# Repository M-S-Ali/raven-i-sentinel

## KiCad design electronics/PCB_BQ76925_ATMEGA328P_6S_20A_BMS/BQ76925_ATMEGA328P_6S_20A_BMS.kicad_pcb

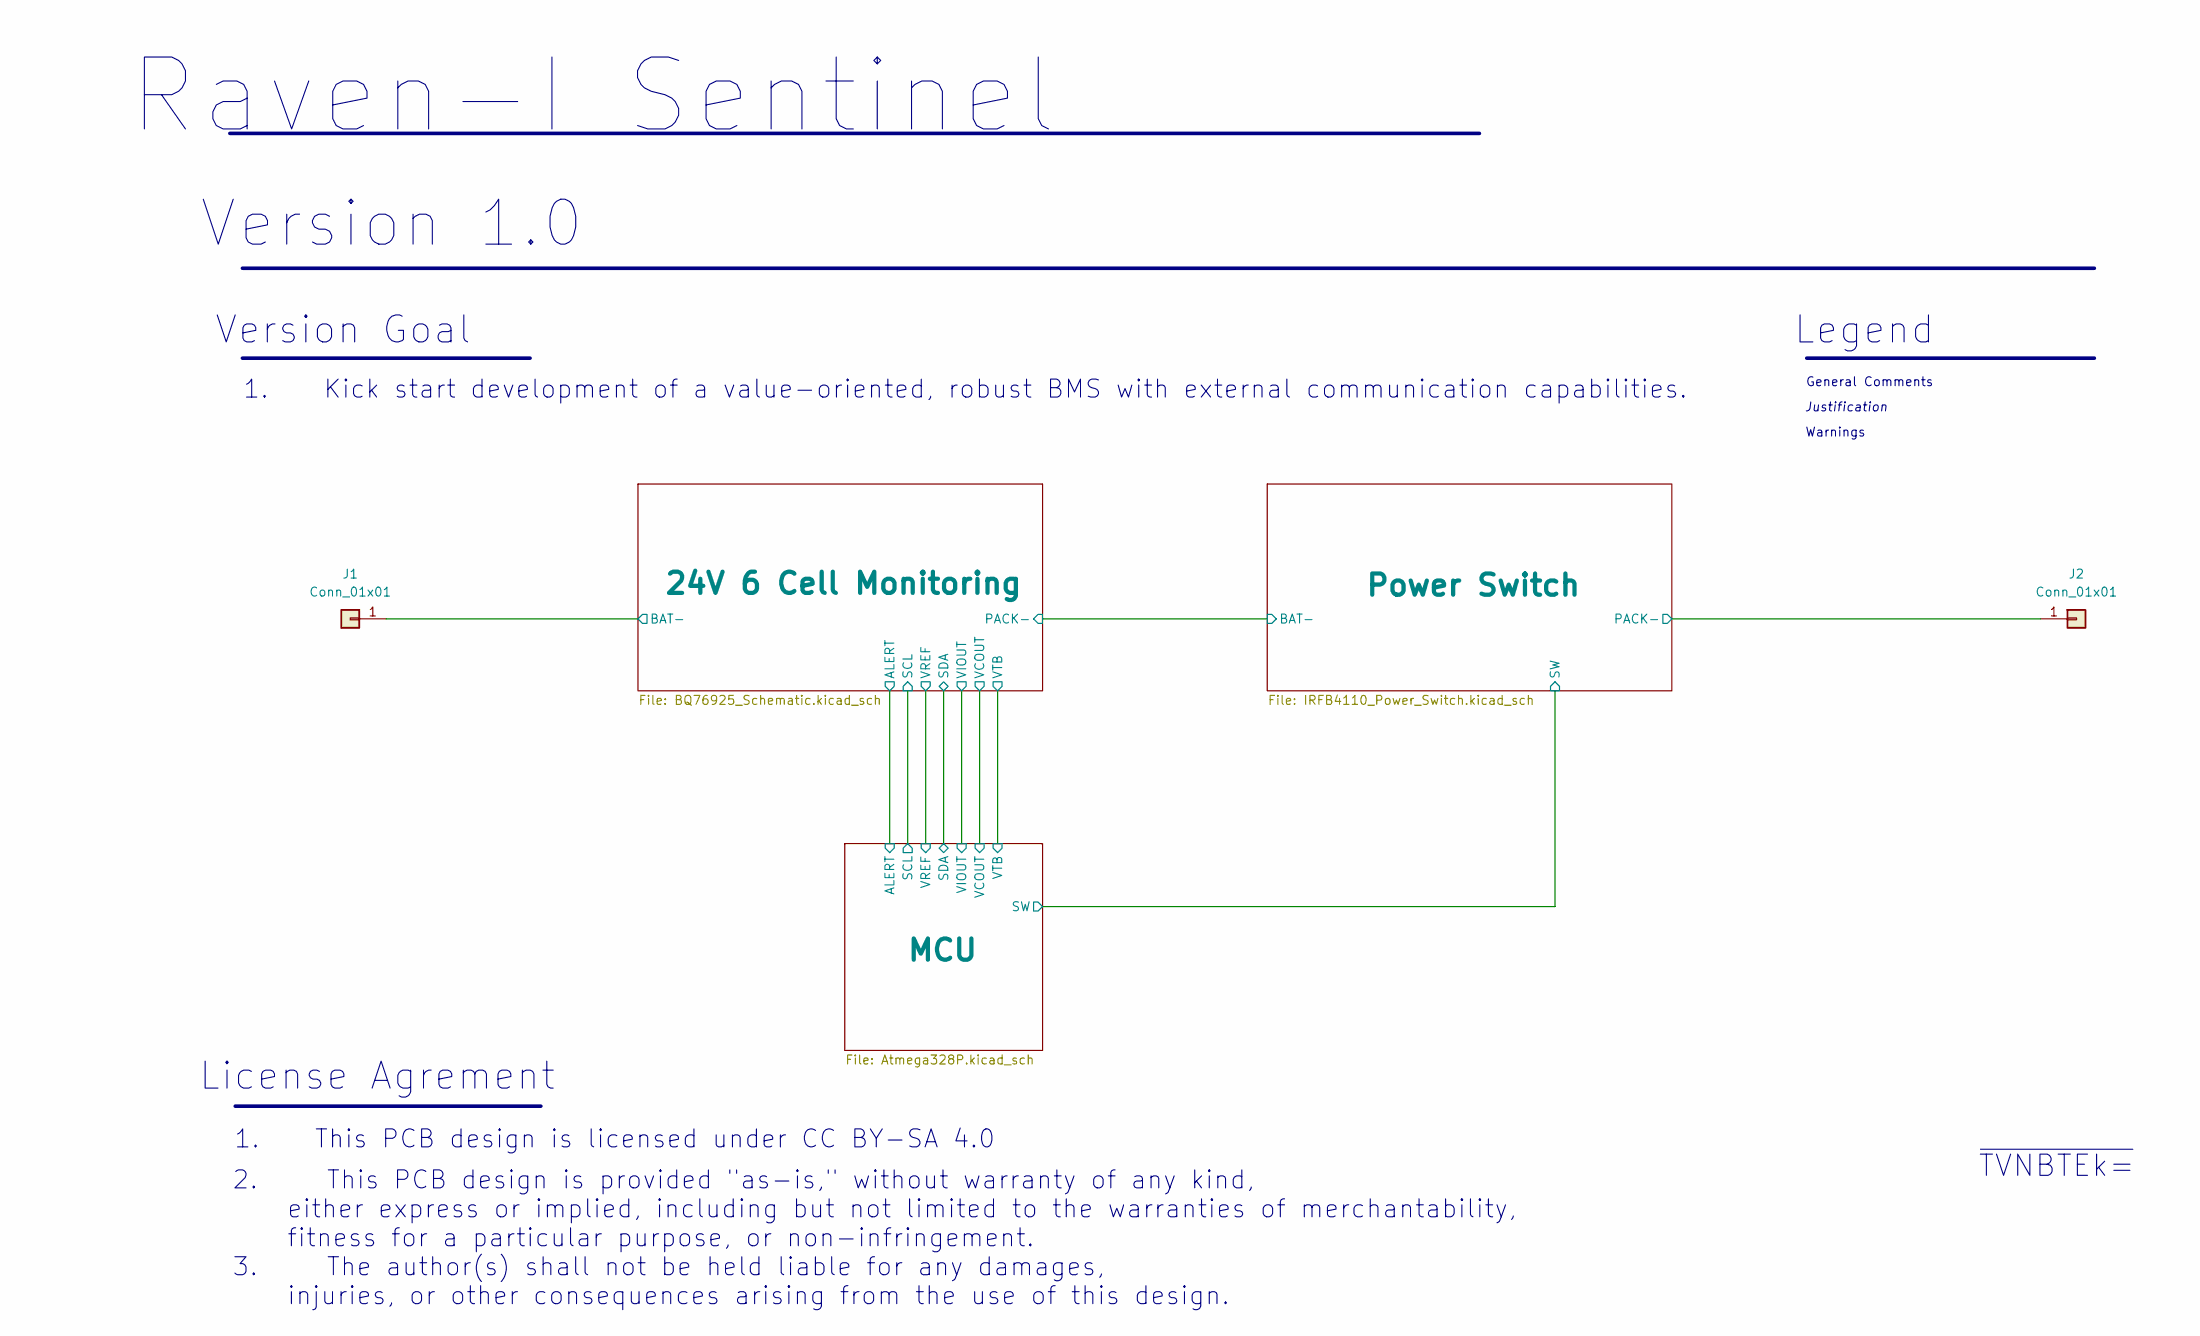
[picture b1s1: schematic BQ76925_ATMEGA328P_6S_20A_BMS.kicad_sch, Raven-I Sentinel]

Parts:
J1, J2: Conn_01x01; SolderWirePad_1x01_SMD_5x10mm

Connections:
/24V 6 Cell Monitoring/BAT-: J1.1; also elsewhere on the board
/Power Switch/PACK-: J2.1; also elsewhere on the board

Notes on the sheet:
1. This PCB design is licensed under CC BY-SA 4.0
Justification
1. Kick start development of a value-oriented, robust BMS with external communication capabilities.
~{TVNBTEk=}
License Agrement
Warnings
2. This PCB design is provided "as-is," without warranty of any kind, either express or implied, including but not limited to the warranties of merchantability, fitness for a particular purpose, or non-infringement. 3. The author(s) shall not be held liable for any damages, injuries, or other conse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
General Comments
Version ${REVISION}
Raven-I Sentinel
Version Goal
Legend

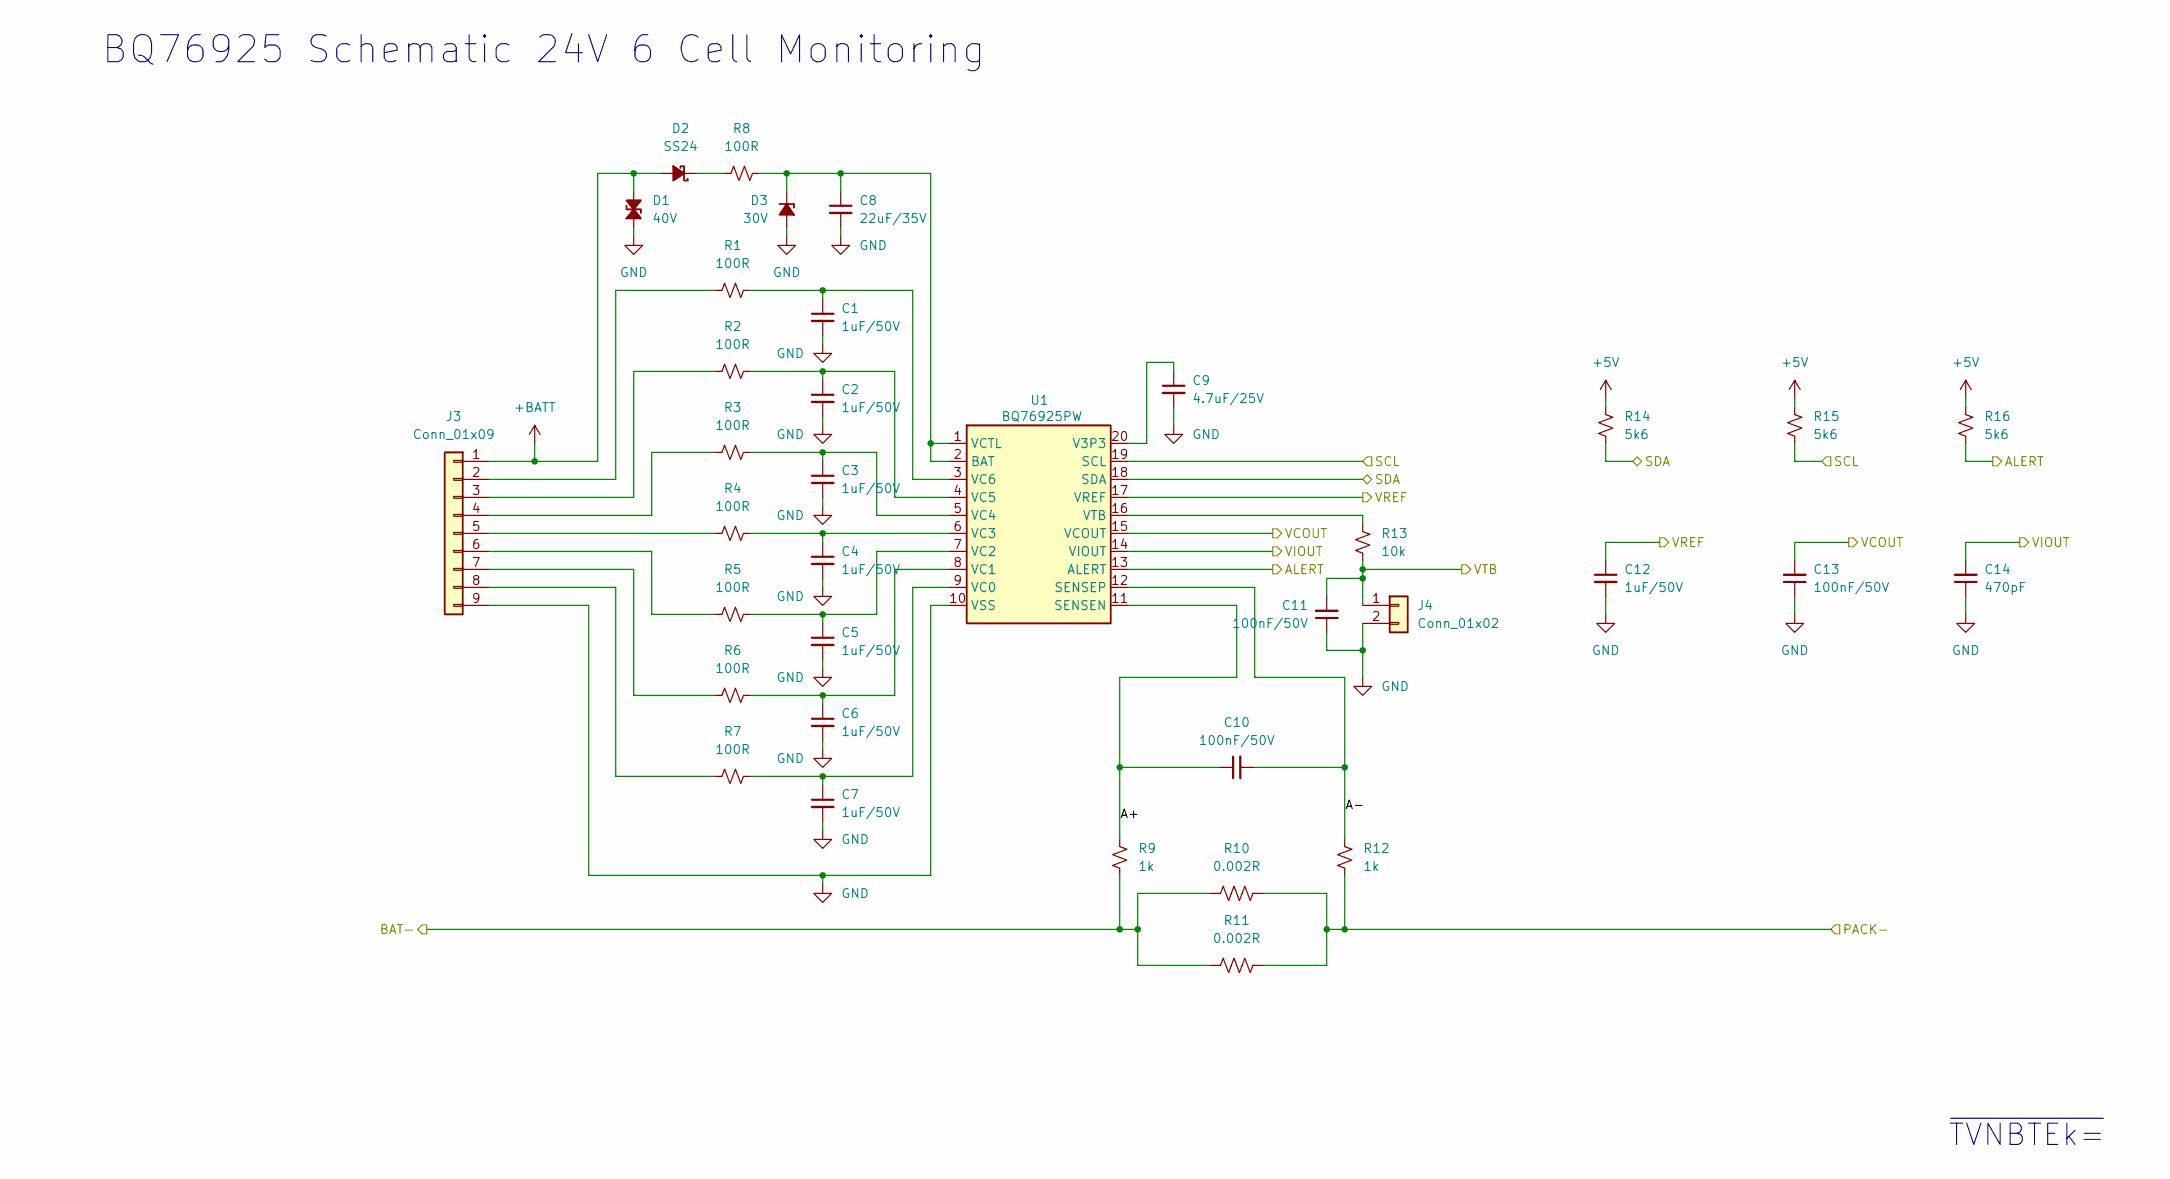
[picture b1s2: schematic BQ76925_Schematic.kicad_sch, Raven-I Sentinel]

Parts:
C1, C2, C3, C4, C5, C6, C7, C12: 1uF/50V; C_0805_2012Metric_Pad1.18x1.45mm_HandSolder
C8: 22uF/35V; CP_Elec_6.3x5.7
C9: 4.7uF/25V; C_0805_2012Metric_Pad1.18x1.45mm_HandSolder
C10, C11, C13: 100nF/50V; C_0805_2012Metric_Pad1.18x1.45mm_HandSolder
C14: 470pF; C_1206_3216Metric_Pad1.33x1.80mm_HandSolder
D1: 40V; D_SMA_Handsoldering
D2: SS24; D_SMB
D3: 30V; D_SOD-123
J3: Conn_01x09; PinHeader_1x09_P2.54mm_Vertical
J4: Conn_01x02; PinHeader_1x02_P2.54mm_Vertical
R1, R2, R3, R4, R5, R6, R7, R8: 100R; R_1206_3216Metric_Pad1.30x1.75mm_HandSolder
R9, R12: 1k; R_0603_1608Metric_Pad0.98x0.95mm_HandSolder
R10, R11: 0.002R; R_2512_6332Metric
R13: 10k; R_0603_1608Metric_Pad0.98x0.95mm_HandSolder
R14, R15, R16: 5k6; R_0603_1608Metric_Pad0.98x0.95mm_HandSolder
U1: BQ76925PW; TSSOP-20_4.4x6.5mm_P0.65mm

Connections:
+5V: R14.2, R15.2, R16.2; also elsewhere on the board
+BATT: D1.2 (A2), D2.2 (A), J3.1; also elsewhere on the board
/24V 6 Cell Monitoring/A+: C10.1, R9.2, U1.11 (SENSEN)
/24V 6 Cell Monitoring/A-: C10.2, R12.2, U1.12 (SENSEP)
/24V 6 Cell Monitoring/ALERT: R16.1, U1.13 (ALERT); also elsewhere on the board
/24V 6 Cell Monitoring/BAT-: R9.1, R10.1, R11.1; also elsewhere on the board
/24V 6 Cell Monitoring/PACK-: R10.2, R11.2, R12.1; also elsewhere on the board
/24V 6 Cell Monitoring/SCL: R15.1, U1.19 (SCL); also elsewhere on the board
/24V 6 Cell Monitoring/SDA: R14.1, U1.18 (SDA); also elsewhere on the board
/24V 6 Cell Monitoring/VCOUT: C13.2, U1.15 (VCOUT); also elsewhere on the board
/24V 6 Cell Monitoring/VIOUT: C14.2, U1.14 (VIOUT); also elsewhere on the board
/24V 6 Cell Monitoring/VREF: C12.1, U1.17 (VREF); also elsewhere on the board
/24V 6 Cell Monitoring/VTB: C11.2, J4.1, R13.1; also elsewhere on the board
GND: C1.2, C2.2, C3.2, C4.2, C5.2, C6.2, C7.2, C8.2, C9.2, C11.1, C12.2, C13.1, C14.1, D1.1 (A1), D3.2 (A), J3.9, J4.2, U1.10 (VSS); also elsewhere on the board
unnamed: D2.1 (K), R8.1
unnamed: C8.1, D3.1 (K), R8.2, U1.1 (VCTL), U1.2 (BAT)
unnamed: J3.2, R1.1
unnamed: J3.3, R2.1
unnamed: J3.4, R3.1
unnamed: J3.5, R4.1
unnamed: J3.6, R5.1
unnamed: J3.7, R6.1
unnamed: J3.8, R7.1
unnamed: C9.1, U1.20 (V3P3)
unnamed: C7.1, R7.2, U1.9 (VC0)
unnamed: C6.1, R6.2, U1.8 (VC1)
unnamed: C5.1, R5.2, U1.7 (VC2)
unnamed: C4.1, R4.2, U1.6 (VC3)
unnamed: C3.1, R3.2, U1.5 (VC4)
unnamed: C2.1, R2.2, U1.4 (VC5)
unnamed: C1.1, R1.2, U1.3 (VC6)
unnamed: R13.2, U1.16 (VTB)

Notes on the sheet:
~{TVNBTEk=}
BQ76925 Schematic 24V 6 Cell Monitoring

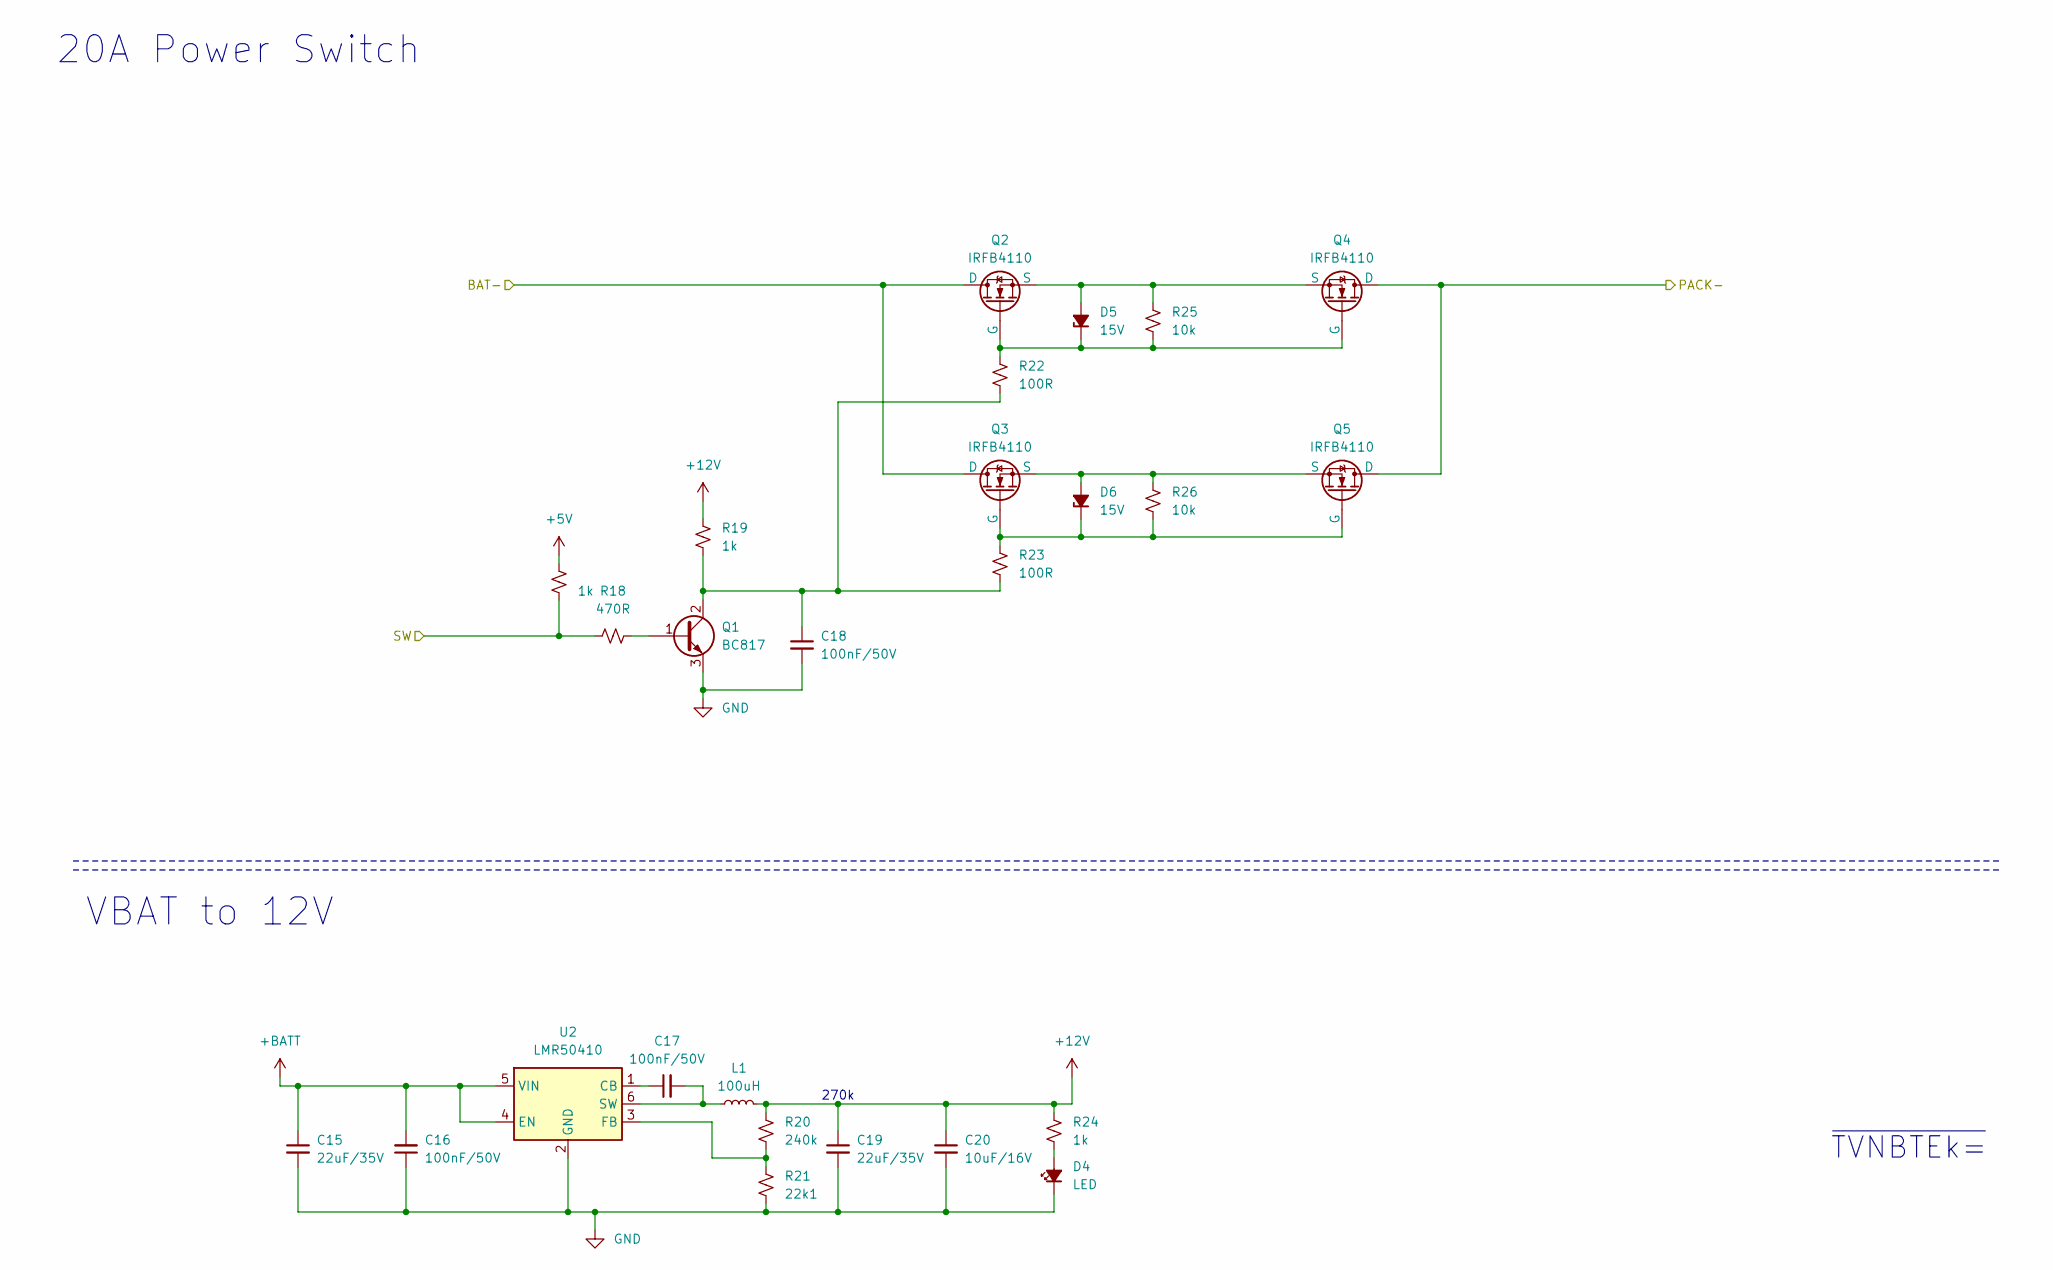
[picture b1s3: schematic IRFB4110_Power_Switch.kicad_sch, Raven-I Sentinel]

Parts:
C15, C19: 22uF/35V; CP_Elec_6.3x5.7
C16, C17, C18: 100nF/50V; C_0805_2012Metric_Pad1.18x1.45mm_HandSolder
C20: 10uF/16V; C_0603_1608Metric_Pad1.08x0.95mm_HandSolder
D4: LED; R_0805_2012Metric_Pad1.20x1.40mm_HandSolder
D5, D6: 15V; D_SOD-123
L1: 100uH; L_7.3x7.3_H3.5
Q1: BC817; SOT-23
Q2, Q3, Q4, Q5: IRFB4110; TO-220-3_Horizontal_TabDown
R17, R19, R24: 1k; R_0603_1608Metric_Pad0.98x0.95mm_HandSolder
R18: 470R; R_0603_1608Metric_Pad0.98x0.95mm_HandSolder
R20: 240k; R_0805_2012Metric_Pad1.20x1.40mm_HandSolder
R21: 22k1; R_0603_1608Metric_Pad0.98x0.95mm_HandSolder
R22, R23: 100R; R_1206_3216Metric_Pad1.30x1.75mm_HandSolder
R25, R26: 10k; R_0603_1608Metric_Pad0.98x0.95mm_HandSolder
U2: LMR50410; SOT-23-6

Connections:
+5V: R17.2; also elsewhere on the board
+12V: C19.1, C20.1, L1.2, R19.2, R20.1, R24.1; also elsewhere on the board
+BATT: C15.1, C16.2, U2.4 (EN), U2.5 (VIN); also elsewhere on the board
/24V 6 Cell Monitoring/PACK-: Q2.2 (D), Q3.2 (D); also elsewhere on the board
/MCU/SW: R17.1, R18.2; also elsewhere on the board
/Power Switch/PACK-: Q4.2 (D), Q5.2 (D); also elsewhere on the board
GND: C15.2, C16.1, C18.2, C19.2, C20.2, D4.1 (K), Q1.3 (E), R21.2, U2.2 (GND); also elsewhere on the board
unnamed: D4.2 (A), R24.2
unnamed: D5.2 (A), Q2.3 (S), Q4.3 (S), R25.2
unnamed: D5.1 (K), Q2.1 (G), Q4.1 (G), R22.1, R25.1
unnamed: D6.2 (A), Q3.3 (S), Q5.3 (S), R26.2
unnamed: D6.1 (K), Q3.1 (G), Q5.1 (G), R23.1, R26.1
unnamed: Q1.1 (B), R18.1
unnamed: C18.1, Q1.2 (C), R19.1, R22.2, R23.2
unnamed: C17.1, U2.1 (CB)
unnamed: R20.2, R21.1, U2.3 (FB)
unnamed: C17.2, L1.1, U2.6 (SW)

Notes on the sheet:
270k
~{TVNBTEk=}
VBAT to 12V
20A Power Switch

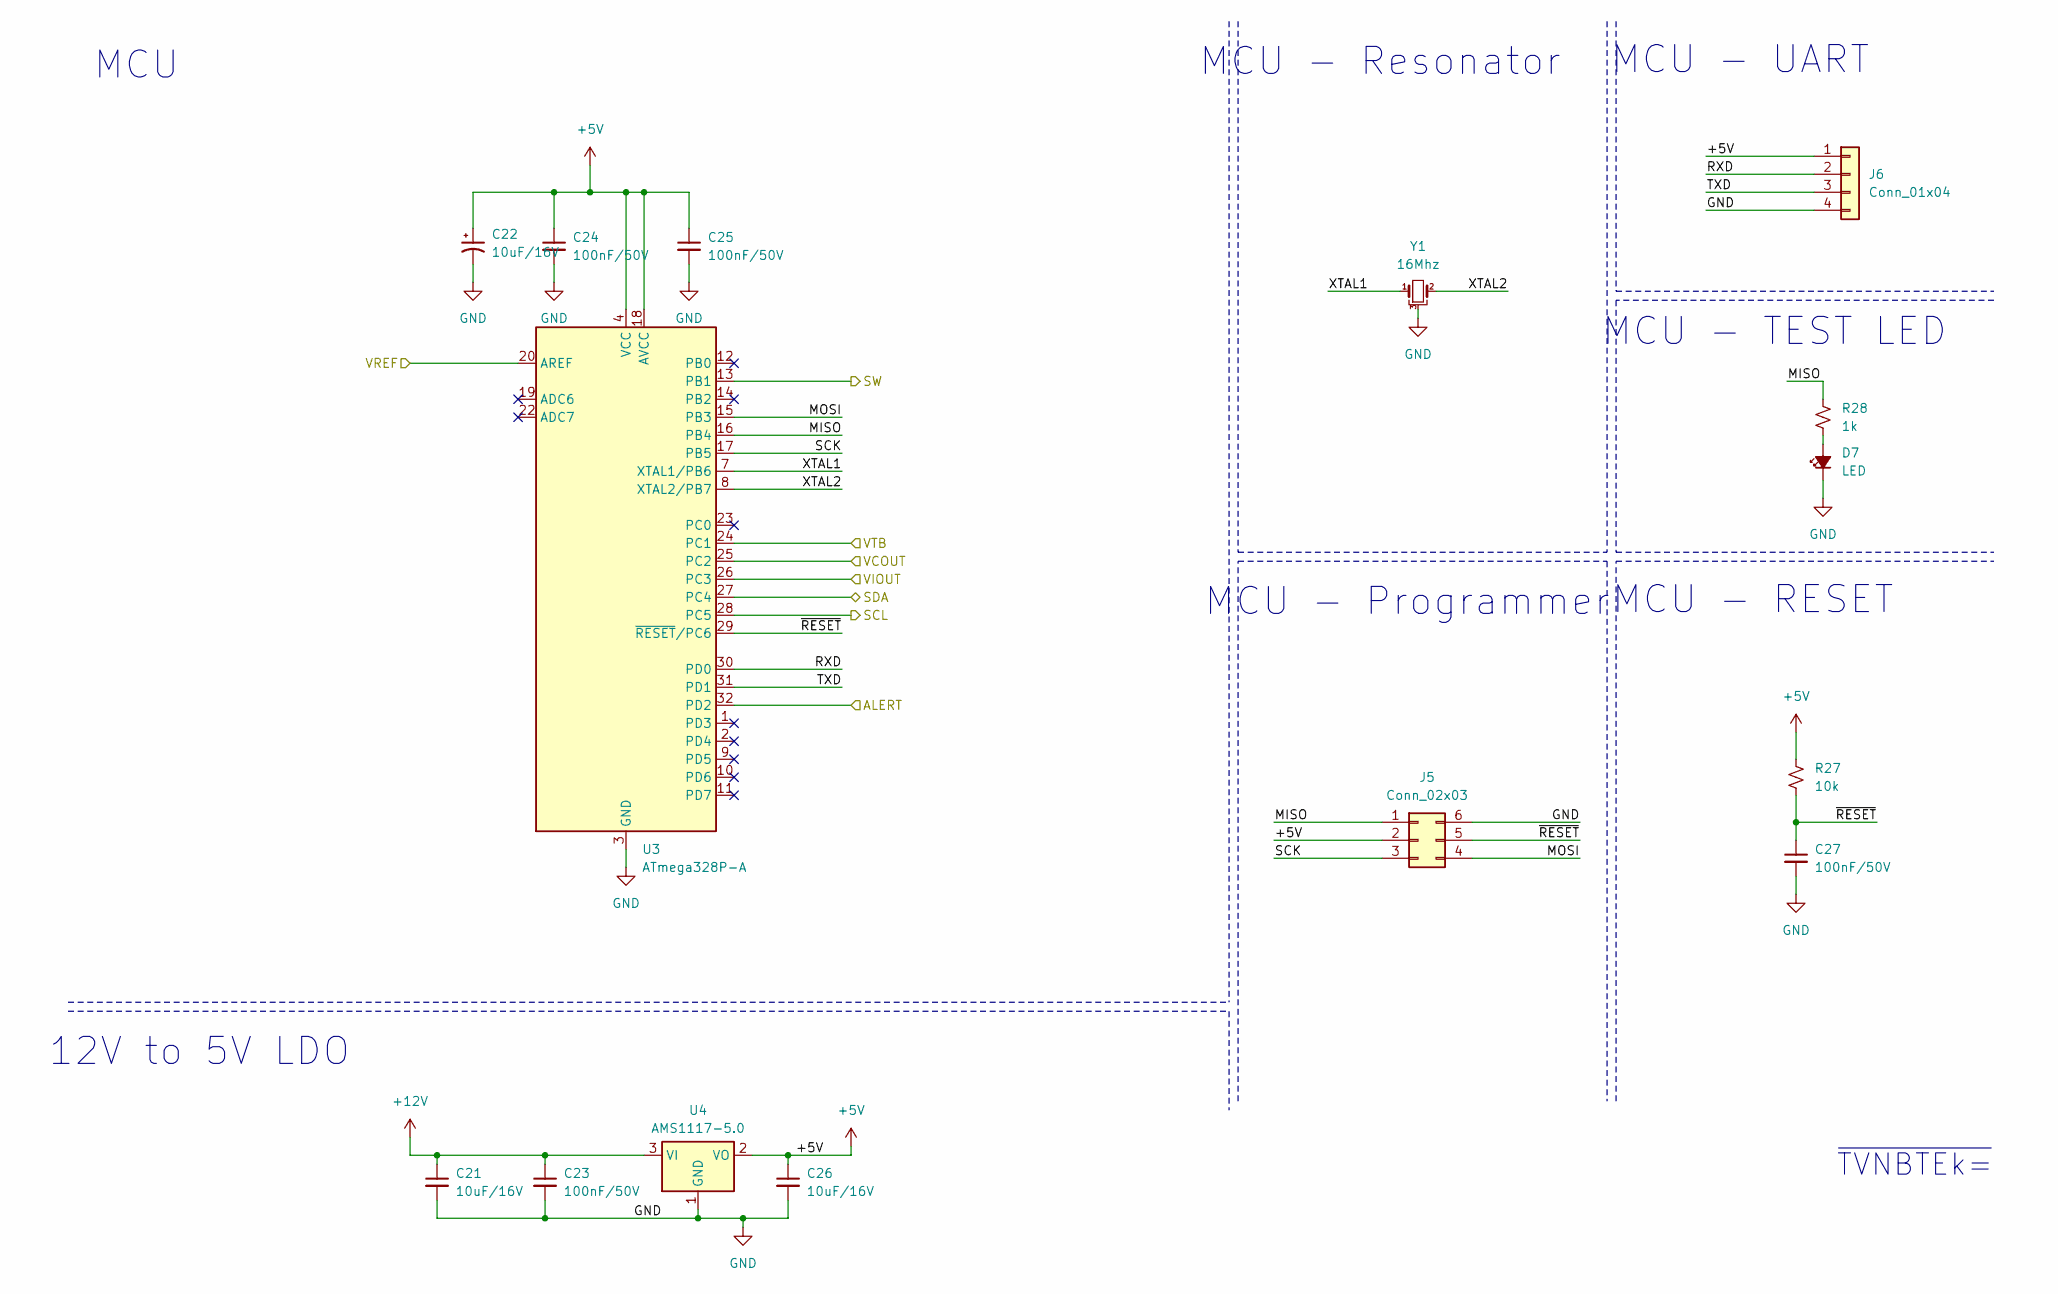
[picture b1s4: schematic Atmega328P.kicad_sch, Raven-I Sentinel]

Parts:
C21, C22, C26: 10uF/16V; C_0603_1608Metric_Pad1.08x0.95mm_HandSolder
C23, C24, C25, C27: 100nF/50V; C_0805_2012Metric_Pad1.18x1.45mm_HandSolder
D7: LED; R_0805_2012Metric_Pad1.20x1.40mm_HandSolder
J5: Conn_02x03; PinHeader_2x03_P2.54mm_Vertical
J6: Conn_01x04; PinHeader_1x04_P2.54mm_Vertical
R27: 10k; R_0603_1608Metric_Pad0.98x0.95mm_HandSolder
R28: 1k; R_0603_1608Metric_Pad0.98x0.95mm_HandSolder
U3: ATmega328P-A; TQFP-32_7x7mm_P0.8mm
U4: AMS1117-5.0; SOT-223-3_TabPin2
Y1: 16Mhz; Resonator_SMD_Murata_CSTxExxV-3Pin_3.0x1.1mm_HandSoldering

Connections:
+5V: C22.1, C24.1, C25.1, C26.1, J5.2, J6.1, R27.2, U3.4 (VCC), U3.6 (VCC), U3.18 (AVCC), U4.2 (VO); also elsewhere on the board
+12V: C21.1, C23.1, U4.3 (VI); also elsewhere on the board
/24V 6 Cell Monitoring/ALERT: U3.32 (PD2); also elsewhere on the board
/24V 6 Cell Monitoring/SCL: U3.28 (PC5); also elsewhere on the board
/24V 6 Cell Monitoring/SDA: U3.27 (PC4); also elsewhere on the board
/24V 6 Cell Monitoring/VCOUT: U3.25 (PC2); also elsewhere on the board
/24V 6 Cell Monitoring/VIOUT: U3.26 (PC3); also elsewhere on the board
/24V 6 Cell Monitoring/VREF: U3.20 (AREF); also elsewhere on the board
/24V 6 Cell Monitoring/VTB: U3.24 (PC1); also elsewhere on the board
/MCU/MISO: J5.1, R28.1, U3.16 (PB4)
/MCU/MOSI: J5.4, U3.15 (PB3)
/MCU/RXD: J6.2, U3.30 (PD0)
/MCU/SCK: J5.3, U3.17 (PB5)
/MCU/SW: U3.13 (PB1); also elsewhere on the board
/MCU/TXD: J6.3, U3.31 (PD1)
/MCU/XTAL1: U3.7 (XTAL1/PB6), Y1.1
/MCU/XTAL2: U3.8 (XTAL2/PB7), Y1.2
/MCU/~RESET: C27.1, J5.5, R27.1, U3.29 (~RESET/PC6)
GND: C21.2, C22.2, C23.2, C24.2, C25.2, C26.2, C27.2, D7.1 (K), J5.6, J6.4, U3.3 (GND), U3.5 (GND), U3.21 (GND), U4.1 (GND), Y1.3; also elsewhere on the board
unnamed: D7.2 (A), R28.2

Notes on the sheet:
~{TVNBTEk=}
MCU - Resonator
MCU
MCU - UART
MCU - TEST LED
MCU - Programmer
MCU - RESET
12V to 5V LDO

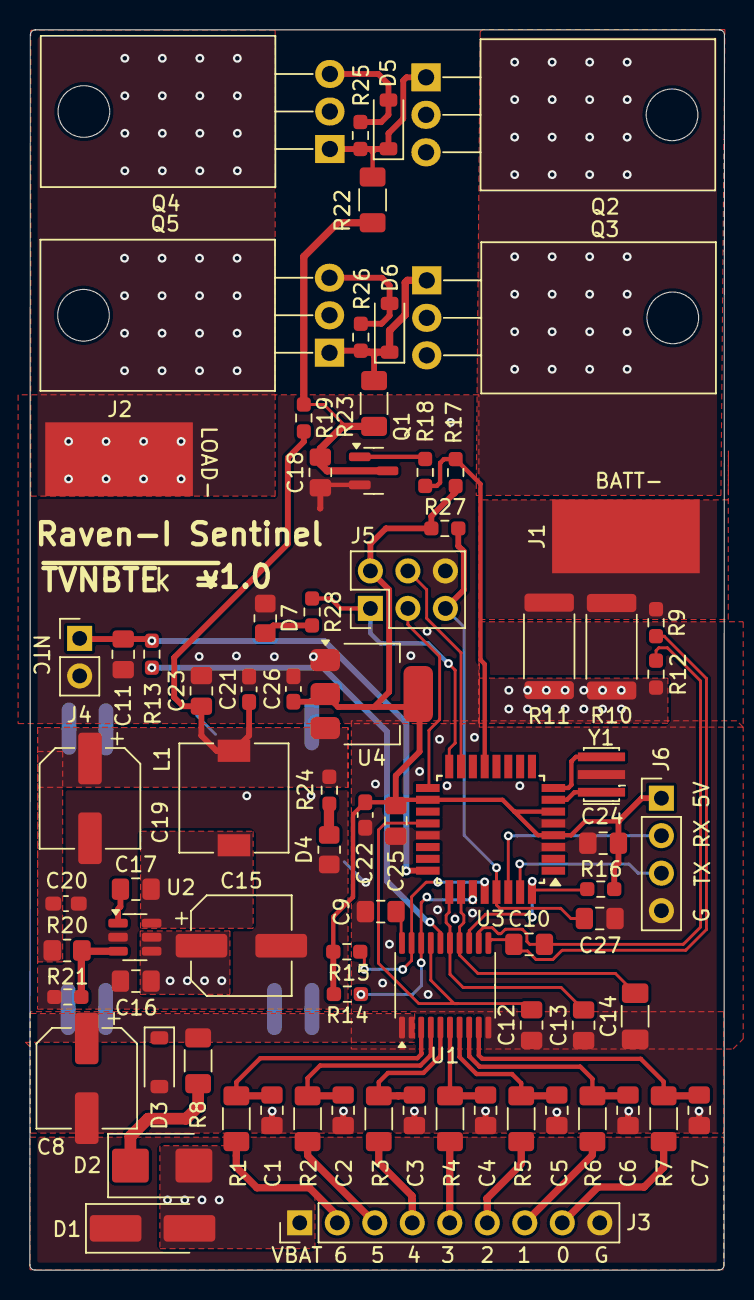
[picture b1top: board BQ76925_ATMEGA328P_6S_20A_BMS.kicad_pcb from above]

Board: 2 copper layers, 47.0 x 84.0 mm, 79 parts (0 on the bottom side), 54 nets.

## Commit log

2024-11-20 project created
2024-11-20 created pcb kicad project and folder structure
2024-11-20 License file included
2024-11-20 included datasheets.md
2024-11-20 updated gitignore to avoid PDF in docs
2024-11-21 included major componenets datasheet in docs
2024-11-21 started with schematic included main components to library
2024-11-22 schematic progress completed AFE, made schematic structure
2024-11-23 schematic completed component need to be finalised
2024-11-23 schematic symbol library updated
2024-11-23 Schematic completed components calculated need to check avaialability
2024-11-24 included mmbt22a transistor datasheet in docs/datasheets
2024-11-24 added power led and mcu test led in schematic
2024-11-25 common footprints assigned to symbols
2024-11-25 schematic components footprint updated
2024-11-26 MCU - Crystal replaced with resonator
2024-11-26 schematic pdf updated. docs/datasheet updated sense resistor and transistor
2024-11-26 pcb design half complete
2024-11-27 routing issue analog pins parallel routing and more length need to plan
2024-11-28 pcb placement and 90 percent routed
2024-11-29 PCB DRC complete footprints library exported. PCB optimization required
2024-11-29 completed pcb layout DRC completed. Final review and sleep with design pending
2024-12-04 3d library made independent
2024-12-04 started software development
2024-12-05 gui strucutre almost visualised
2024-12-06 code rivised with chatgpt
2024-12-07 started working on simple gui serial interface to be used for testing
2025-01-31 PCB design ver 1.0 archived
2025-07-05 saved pcb as new kicad version
2025-07-06 basic working firmware with rtos added
    need to add cell bal code, test i2c, document
2025-07-06 added a program in tests to dump all register data in bq76925
2025-07-07 data dump updated
2025-07-20 driver development and calibration in progress
2025-07-20 vcn calibration applied
2025-07-21 gui working
2025-07-22 started to implement cell balancing
2025-07-23 lisense terms updated
